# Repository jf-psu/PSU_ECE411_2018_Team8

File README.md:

# PSU_ECE411_2018_Team8
Fall 2018 Practicum Project for Portland State University

Please see the [Wiki](https://github.com/jf-psu/PSU_ECE411_2018_Team8/wiki) for more information.

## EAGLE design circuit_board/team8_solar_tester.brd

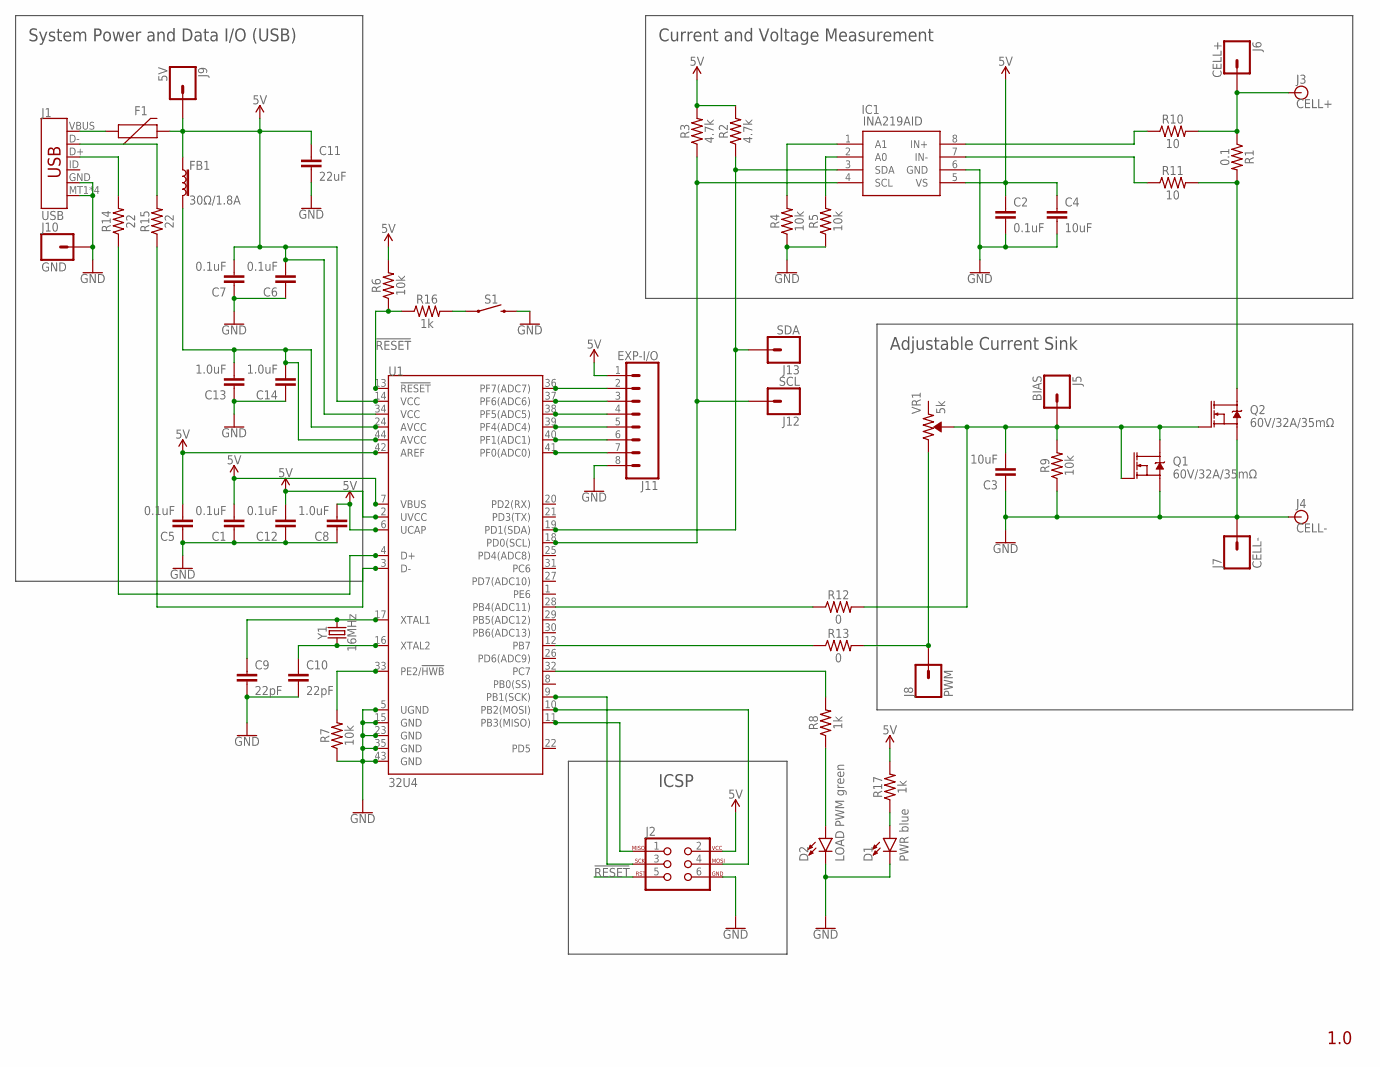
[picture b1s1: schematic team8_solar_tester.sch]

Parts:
C1, C2, C5, C6, C7, C12: 0.1uF; 0603
C3, C4: 10uF; 0805
C8, C13, C14: 1.0uF; 0603
C9, C10: 22pF; 0603
C11: 22uF; 0805
D1: PWR blue; LED-0603
D2: LOAD PWM green; LED-0603
F1: PPTC_6V500MA; 0805
FB1: 30Ω/1.8A; 0603
IC1: INA219AID; SOIC127P600X175-8N
J1: USB; USB-MICROB
J2: AVR_SPI_PROG_3X2PTH; 2X3
J3: CELL+; BANANA_CONN
J4: CELL-; BANANA_CONN
J5: BIAS; 1X01
J6: CELL+; 1X01
J7: CELL-; 1X01
J8: PWM; 1X01
J9: 5V; 1X01
J10: GND; 1X01
J11: EXP-I/O; 1X08_LONGPADS
J12: SCL; 1X01
J13: SDA; 1X01
Q1, Q2: 60V/32A/35mΩ; TO220V
R1: 0.1; 1210
R2, R3: 4.7k; 0603
R4, R5, R6, R7, R9: 10k; 0603
R8, R16, R17: 1k; 0603
R10, R11: 10; 0603
R12, R13: 0; 0603
R14, R15: 22; 0603
S1: MOMENTARY-SWITCH-SPST-PTH-6.0MM; TACTILE_SWITCH_PTH_6.0MM
U1: 32U4; QFN-44
VR1: 5k; TRIMPOT-SMD-5MM
Y1: 16MHz; CRYSTAL-SMD-5X3.2-4PAD

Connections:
5V: C1.2, C2.1, C4.1, C5.2, C6.2, C7.2, C8.2, C11.1, C12.2, F1.2, FB1.1, IC1.5 (VS), J2.2, J9.1, J11.1, R2.2, R3.2, R6.2, R17.2, U1.2 (UVCC), U1.6 (UCAP), U1.7 (VBUS), U1.14 (VCC), U1.34 (VCC), U1.42 (AREF)
!RESET!: J2.5, R6.1, R16.1, U1.13 (!RESET)
AVCC: C13.2, C14.2, FB1.2, U1.24 (AVCC), U1.44 (AVCC)
BEFORE_FUSE: F1.1, J1.VBUS
GND: C1.1, C2.2, C3.1, C4.2, C5.1, C6.1, C7.1, C8.1, C9.2, C10.2, C11.2, C12.1, C13.1, C14.1, D1.C, D2.C, IC1.6 (GND), J1.GND, J1.MT1 (SHIELD), J1.MT2 (SHIELD), J1.P$1 (SHIELD), J1.P$2 (SHIELD), J2.6, J4.P$1, J7.1, J10.1, J11.8, Q1.3 (S), Q2.3 (S), R4.1, R5.1, R7.1, R9.1, S1.3 (2), U1.5 (UGND), U1.15 (GND), U1.23 (GND), U1.35 (GND), U1.43 (GND)
unnamed: Q2.2 (D), R1.2, R11.2
unnamed: J3.P$1, J6.1, R1.1, R10.2
unnamed: IC1.2 (A0), R5.2
unnamed: IC1.1 (A1), R4.2
unnamed: J11.7, U1.41 (PF0(ADC0))
unnamed: IC1.4 (SCL), J12.1, R3.1, U1.18 (PD0(SCL))
unnamed: IC1.8 (IN+), R10.1
unnamed: IC1.7 (IN-), R11.1
unnamed: R13.1, U1.12 (PB7)
unnamed: J2.1, U1.11 (PB3(MISO))
unnamed: J2.4, U1.10 (PB2(MOSI))
unnamed: J2.3, U1.9 (PB1(SCK))
unnamed: R12.1, U1.28 (PB4(ADC11))
unnamed: J8.1, R13.2, VR1.C (CW)
unnamed: J1.D+, R14.2
unnamed: J1.D-, R15.2
unnamed: J11.6, U1.40 (PF1(ADC1))
unnamed: R15.1, U1.3 (D-)
unnamed: R14.1, U1.4 (D+)
unnamed: C10.1, U1.16 (XTAL2), Y1.1
unnamed: C9.1, U1.17 (XTAL1), Y1.3 (2)
unnamed: R16.2, S1.1
unnamed: IC1.3 (SDA), J13.1, R2.1, U1.19 (PD1(SDA))
unnamed: C3.2, J5.1, Q1.1 (G), Q1.2 (D), Q2.1 (G), R9.2, R12.2, VR1.B (WIPER)
unnamed: J11.5, U1.39 (PF4(ADC4))
unnamed: J11.4, U1.38 (PF5(ADC5))
unnamed: J11.3, U1.37 (PF6(ADC6))
unnamed: J11.2, U1.36 (PF7(ADC7))
unnamed: R7.2, U1.33 (PE2/!HWB)
unnamed: R8.2, U1.32 (PC7)
unnamed: D2.A, R8.1
unnamed: D1.A, R17.1

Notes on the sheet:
Current and Voltage Measurement
Adjustable Current Sink
ICSP
System Power and Data I/O (USB)

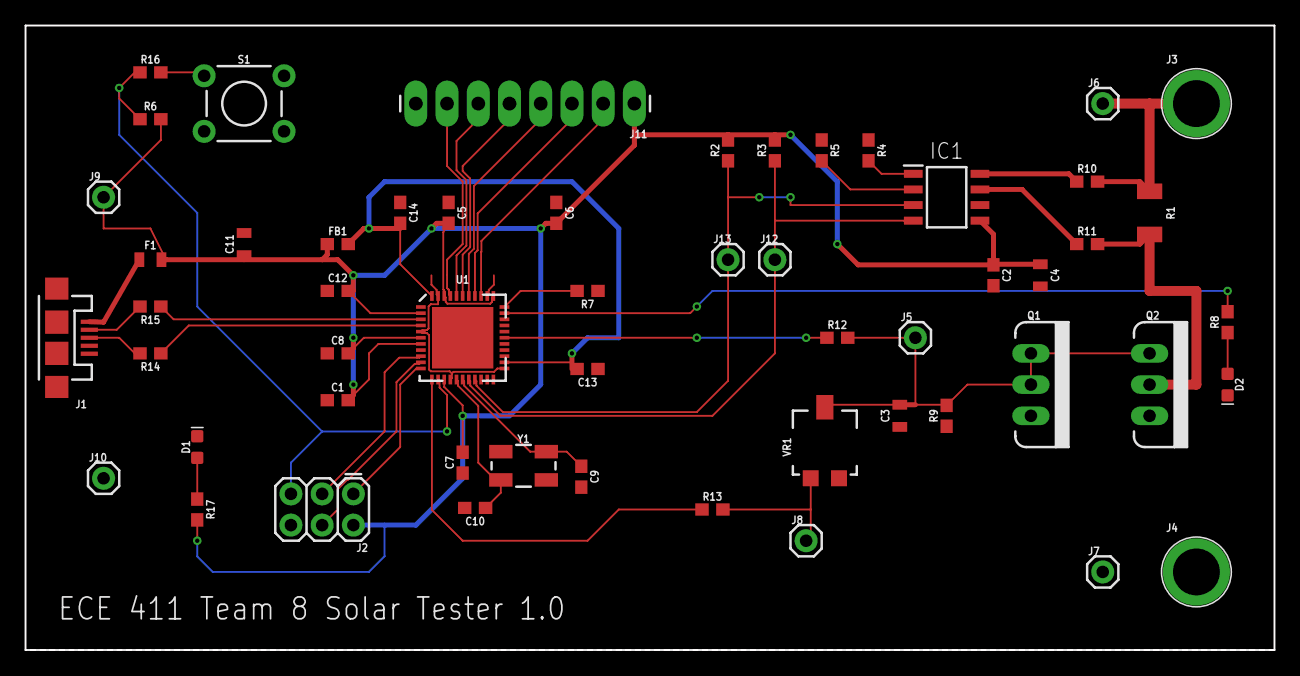
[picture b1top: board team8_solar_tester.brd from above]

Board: 2 copper layers, 101.6 x 50.8 mm, 55 parts (0 on the bottom side), 37 nets.

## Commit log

2018-10-10 Added wiki link to README.md
2018-10-11 converted proposals to pdf
2018-10-25 Update schematics/solar_tester.sch
    First rough draft based on Arduino Micro design.
2018-10-28 Update documents/solar_cell_tester_product_design_specification.pdf
    Adding PDS for solar tester
2018-11-15 Adding the final schematic and board
2018-12-03 Adding BOM
2018-12-03 Adding PDF version of schematic
2018-12-03 Main code
2018-12-03 Added power sensor reading command
2018-12-03 Create counter arduino
2018-12-04 Beta Gen2 UI based on PyQtGraph
2018-12-04 UI basic functions working
2018-12-04 Reduced delays and average count to improve performance
2018-12-04 Added support for reading real data from serial port
2018-12-05 Do averaging on PC rather than device
2018-12-05 Adding picture of board layout

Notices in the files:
parts and their libraries:
SparkFun-Capacitors: Licensing: Creative Commons ShareAlike 4.0 International - https://creativecommons.org/licenses/by-sa/4.0
